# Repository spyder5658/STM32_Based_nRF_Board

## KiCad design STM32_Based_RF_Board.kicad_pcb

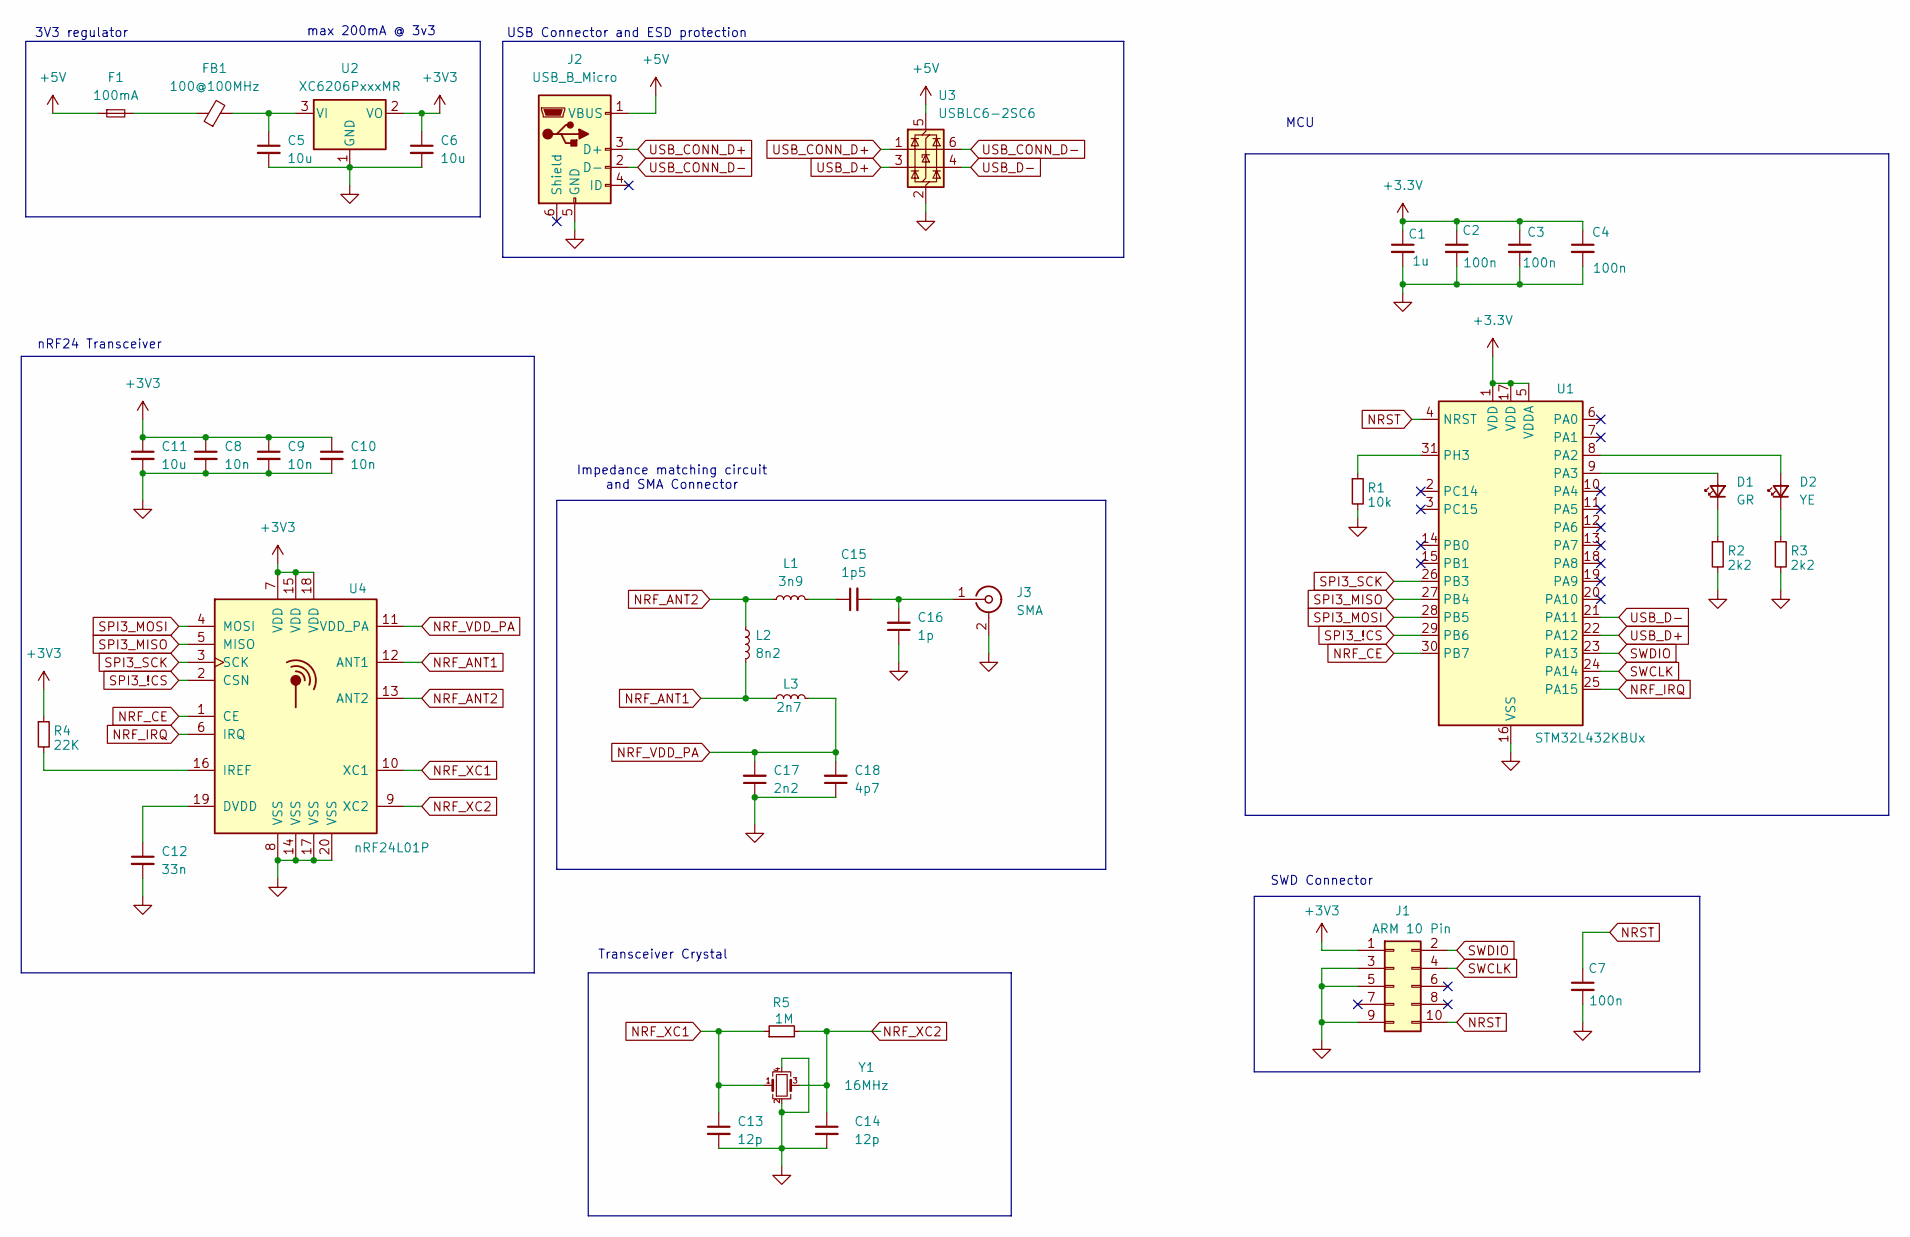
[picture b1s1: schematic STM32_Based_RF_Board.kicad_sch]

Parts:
C1: 1u; C_0402_1005Metric
C2, C3, C4, C7: 100n; C_0402_1005Metric
C5, C6, C11: 10u; C_0603_1608Metric
C8, C9, C10: 10n; C_0402_1005Metric
C12: 33n; C_0402_1005Metric
C13, C14: 12p; C_0402_1005Metric
C15: 1p5; C_0402_1005Metric
C16: 1p; C_0402_1005Metric
C17: 2n2; C_0402_1005Metric
C18: 4p7; C_0402_1005Metric
D1: GR; LED_0603_1608Metric
D2: YE; LED_0603_1608Metric
F1: 100mA; Fuse_1206_3216Metric
FB1: 100@100MHz; L_0805_2012Metric
J1: ARM 10 Pin; PinHeader_2x05_P1.27mm_Vertical
J2: USB_B_Micro; USB_Micro-B_Molex-105017-0001
J3: SMA; SMA_Samtec_SMA-J-P-H-ST-EM1_EdgeMount
L1: 3n9; L_0402_1005Metric
L2: 8n2; L_0402_1005Metric
L3: 2n7; L_0402_1005Metric
R1: 10k; R_0402_1005Metric
R2, R3: 2k2; R_0402_1005Metric
R4: 22K; R_0402_1005Metric
R5: 1M; R_0402_1005Metric
U1: STM32L432KBUx; QFN-32-1EP_5x5mm_P0.5mm_EP3.45x3.45mm
U2: XC6206PxxxMR; SOT-23-3
U3: USBLC6-2SC6; SOT-23-6
U4: nRF24L01P; QFN-20-1EP_4x4mm_P0.5mm_EP2.5x2.5mm
Y1: 16MHz; Crystal_SMD_3225-4Pin_3.2x2.5mm

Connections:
+3.3V: C1.1, C2.1, C3.1, C4.1, U1.1 (VDD), U1.5 (VDDA), U1.17 (VDD)
+3V3: C6.1, C8.1, C9.1, C10.1, C11.1, J1.1, R4.1, U2.2 (VO), U4.7 (VDD), U4.15 (VDD), U4.18 (VDD)
+5V: F1.1, J2.1 (VBUS), U3.5 (VBUS)
GND: C1.2, C2.2, C3.2, C4.2, C5.2, C6.2, C7.2, C8.2, C9.2, C10.2, C11.2, C12.2, C13.2, C14.2, C16.1, C17.1, C18.1, J1.3, J1.5, J1.9, J2.5 (GND), J3.2 (Ext), R1.2, R2.2, R3.2, U1.16 (VSS), U1.32 (VSS), U1.33 (VSS), U2.1 (GND), U3.2 (GND), U4.8 (VSS), U4.14 (VSS), U4.17 (VSS), U4.20 (VSS), Y1.2, Y1.4
NRF_ANT1: L2.2, L3.1, U4.12 (ANT1)
NRF_ANT2: L1.1, L2.1, U4.13 (ANT2)
NRF_CE: U1.30 (PB7), U4.1 (CE)
NRF_IRQ: U1.25 (PA15), U4.6 (IRQ)
NRF_VDD_PA: C17.2, C18.2, L3.2, U4.11 (VDD_PA)
NRF_XC1: C13.1, R5.1, U4.10 (XC1), Y1.1
NRF_XC2: C14.1, R5.2, U4.9 (XC2), Y1.3
NRST: C7.1, J1.10, U1.4 (NRST)
unnamed: C15.1, L1.2
unnamed: D1.2 (A), U1.9 (PA3)
unnamed: D1.1 (K), R2.1
unnamed: D2.2 (A), U1.8 (PA2)
unnamed: D2.1 (K), R3.1
unnamed: F1.2, FB1.1
unnamed: C15.2, C16.2, J3.1 (In)
unnamed: R1.1, U1.31 (PH3)
unnamed: C5.1, FB1.2, U2.3 (VI)
unnamed: C12.1, U4.19 (DVDD)
unnamed: R4.2, U4.16 (IREF)
SPI3_!CS: U1.29 (PB6), U4.2 (CSN)
SPI3_MISO: U1.27 (PB4), U4.5 (MISO)
SPI3_MOSI: U1.28 (PB5), U4.4 (MOSI)
SPI3_SCK: U1.26 (PB3), U4.3 (SCK)
SWCLK: J1.4, U1.24 (PA14)
SWDIO: J1.2, U1.23 (PA13)
USB_CONN_D+: J2.3 (D+), U3.1 (I/O1)
USB_CONN_D-: J2.2 (D-), U3.6 (I/O1)
USB_D+: U1.22 (PA12), U3.3 (I/O2)
USB_D-: U1.21 (PA11), U3.4 (I/O2)

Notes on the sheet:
SWD Connector
Transceiver Crystal
USB Connector and ESD protection
max 200mA @ 3v3
3V3 regulator
Impedance matching circuit and SMA Connector
MCU
nRF24 Transceiver

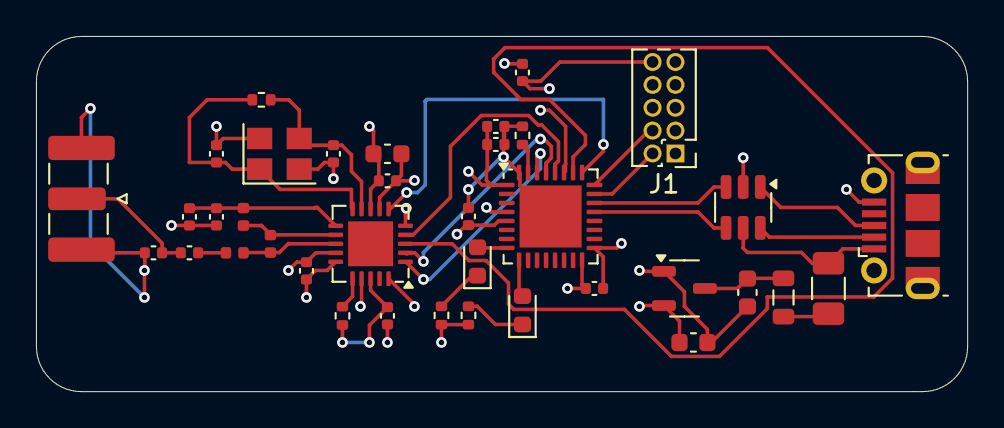
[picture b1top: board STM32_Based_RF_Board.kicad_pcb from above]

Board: 4 copper layers, 51.7 x 19.7 mm, 37 parts (0 on the bottom side), 32 nets.

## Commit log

2024-11-16 Complete RF board commit
